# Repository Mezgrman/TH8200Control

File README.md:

# What's this?
A custom controller board for the Siemens TH8200 hand dryer.

# BOM
You can find the interactive BOM [here](https://mezgrman.github.io/TH8200Control/Hardware/bom/ibom.html).

# Pictures

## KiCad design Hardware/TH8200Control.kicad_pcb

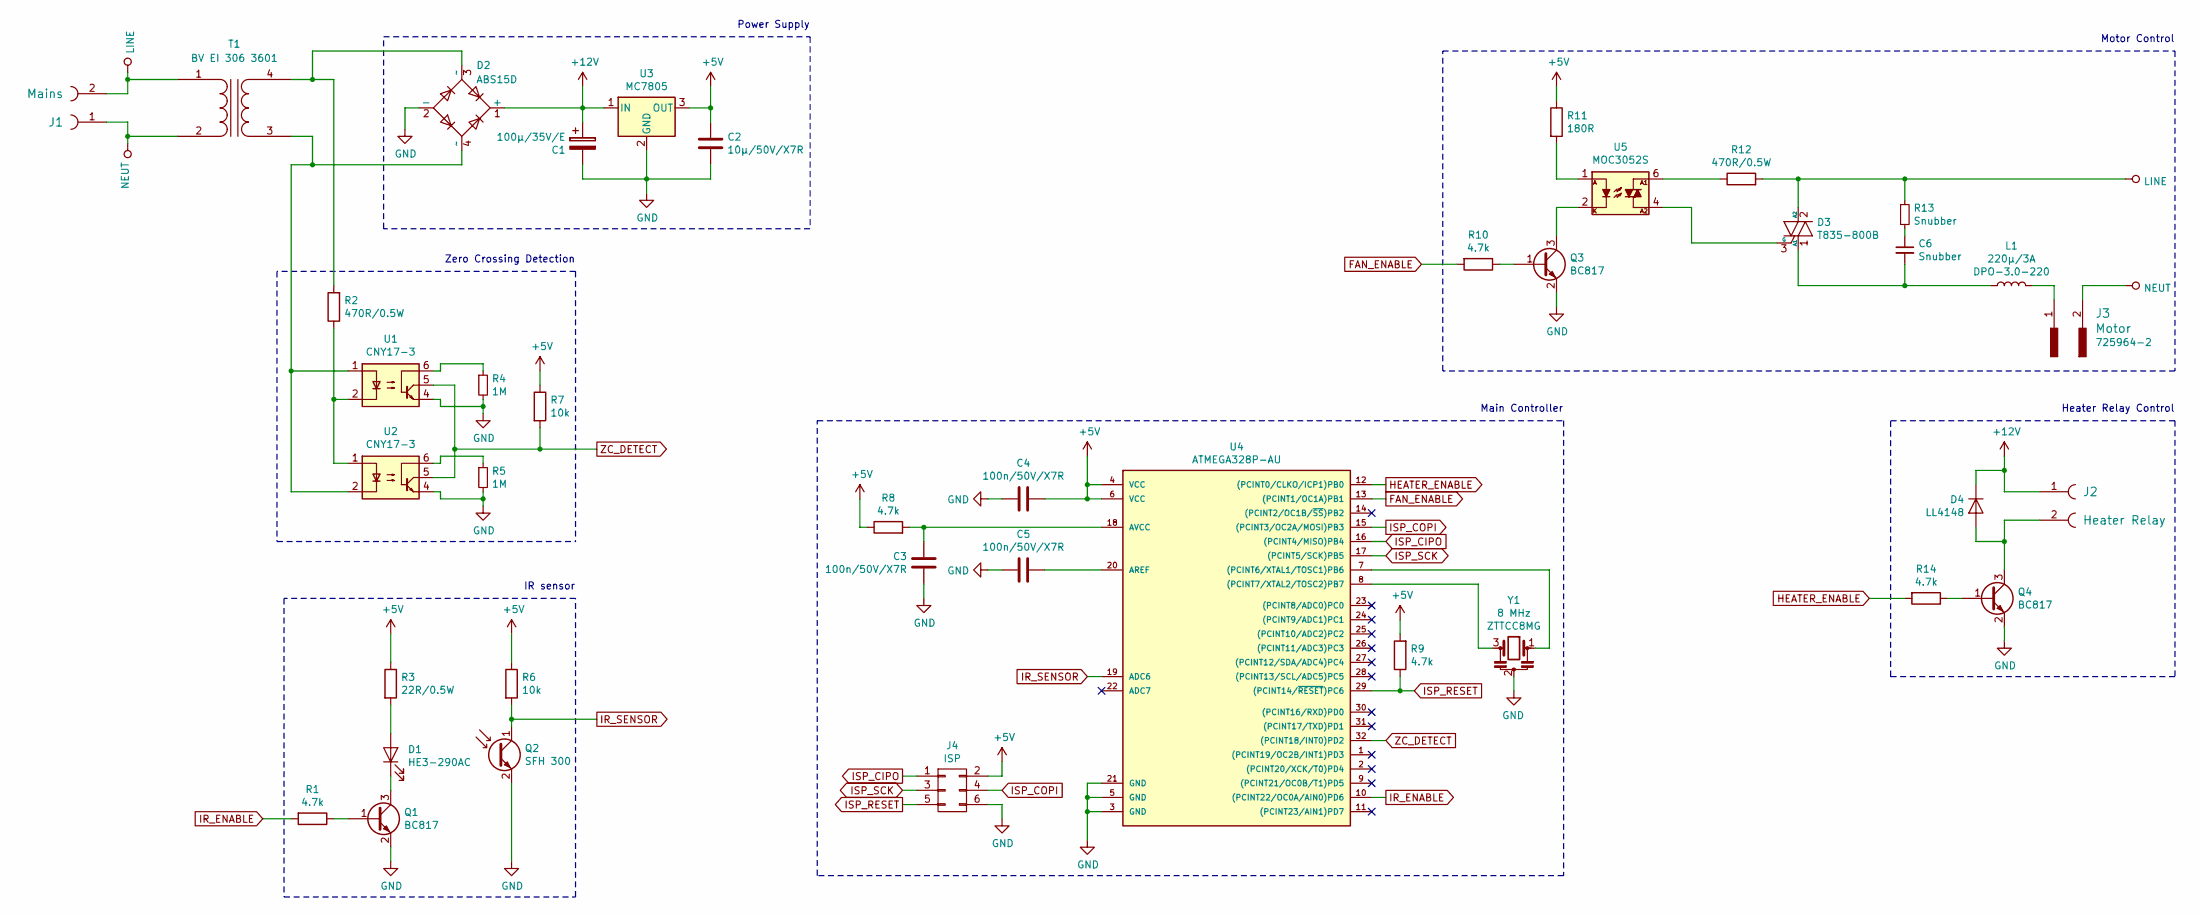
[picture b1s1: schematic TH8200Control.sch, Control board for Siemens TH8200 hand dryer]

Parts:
C1: 100µ/35V/E; CP_Elec_6.3x7.7
C2: 10µ/50V/X7R; C_1206
C3, C4, C5: 100n/50V/X7R; C_0603
C6: Snubber; C_0805
D1: HE3-290AC; LED_D5.0mm_Horicontal_O5.08mm
D2: ABS15D; Rectifier_SMD_4pin_ABS
D3: T835-800B; TO-252-2Lead
D4: LL4148; D_MiniMELF_Standard
J1: Mains; 2_Cables_D1.5mm_P10mm
J2: Heater Relay; 2_Cables_D1.5mm_P10mm
J3: Motor; FASTON_2pin_6.3x0.8mm_P10mm
J4: ISP; Pin_Header_Straight_SMT_02x03
L1: 220µ/3A; Choke_Toroid_13x29mm_Vertical
Q1, Q3, Q4: BC817; SOT-23
Q2: SFH 300; LED_D5.0mm_Horicontal_O5.08mm
R1, R8, R9, R10, R14: 4.7k; R_0603
R2, R12: 470R/0.5W; R_1206
R3: 22R/0.5W; R_1206
R4, R5: 1M; R_0603
R6, R7: 10k; R_0603
R11: 180R; R_0603
R13: Snubber; R_0603
T1: BV EI 306 3601; Transformer_Hahn_BVEI3063601
U1, U2: CNY17-3; Optocoupler_SMD_6pin
U3: MC7805; TO-263-3Lead
U4: ATMEGA328P-AU; TQFP-32_7x7mm_Pitch0.8mm
U5: MOC3052S; Optocoupler_SMD_6pin
Y1: 8 MHz; Resonator_ZTTCC_X.XX_MG

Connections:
+5V: C2.1, C4.1, J4.2, R3.1, R6.1, R7.1, R8.1, R9.2, R11.1, U3.3 (OUT), U4.4 (VCC), U4.6 (VCC)
+12V: C1.1, D2.1 (+), D4.1 (K), J2.1, U3.1 (IN)
FAN_ENABLE: R10.2, U4.13 ((PCINT1/OC1A)PB1)
GND: C1.2, C2.2, C3.1, C4.2, C5.2, D2.2 (-), J4.6, Q1.2 (E), Q2.2 (E), Q3.2 (E), Q4.2 (E), R4.2, R5.2, U1.4, U2.4, U3.2 (GND), U4.3 (GND), U4.5 (GND), U4.21 (GND), Y1.2
HEATER_ENABLE: R14.2, U4.12 ((PCINT0/CLKO/ICP1)PB0)
IR_ENABLE: R1.2, U4.10 ((PCINT22/OC0A/AIN0)PD6)
IR_SENSOR: Q2.1 (C), R6.2, U4.19 (ADC6)
ISP_CIPO: J4.1, U4.16 ((PCINT4/MISO)PB4)
ISP_COPI: J4.4, U4.15 ((PCINT3/OC2A/MOSI)PB3)
ISP_RESET: J4.5, R9.1, U4.29 ((PCINT14/~RESET~)PC6)
ISP_SCK: J4.3, U4.17 ((PCINT5/SCK)PB5)
LINE: D3.2 (A2), J1.2, R12.2, R13.1, T1.1 (AA)
NEUT: J1.1, J3.2, T1.2 (AB)
unnamed: C3.2, R8.2, U4.18 (AVCC)
unnamed: C5.1, U4.20 (AREF)
unnamed: C6.1, R13.2
unnamed: C6.2, D3.1 (A1), L1.1
unnamed: D1.1 (K), Q1.3 (C)
unnamed: D1.2 (A), R3.2
unnamed: D2.3 (~~), R2.2, T1.4 (SB)
unnamed: D2.4 (~~), T1.3 (SA), U1.1, U2.2
unnamed: D3.3 (G), U5.4
unnamed: D4.2 (A), J2.2, Q4.3 (C)
unnamed: J3.1, L1.2
unnamed: Q1.1 (B), R1.1
unnamed: Q3.1 (B), R10.1
unnamed: Q3.3 (C), U5.2
unnamed: Q4.1 (B), R14.1
unnamed: R2.1, U1.2, U2.1
unnamed: R4.1, U1.6
unnamed: R5.1, U2.6
unnamed: R11.2, U5.1
unnamed: R12.1, U5.6
unnamed: U4.7 ((PCINT6/XTAL1/TOSC1)PB6), Y1.1
unnamed: U4.8 ((PCINT7/XTAL2/TOSC2)PB7), Y1.3
ZC_DETECT: R7.2, U1.5, U2.5, U4.32 ((PCINT18/INT0)PD2)

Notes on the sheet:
Zero Crossing Detection
Power Supply
Motor Control
Heater Relay Control
IR sensor
Main Controller

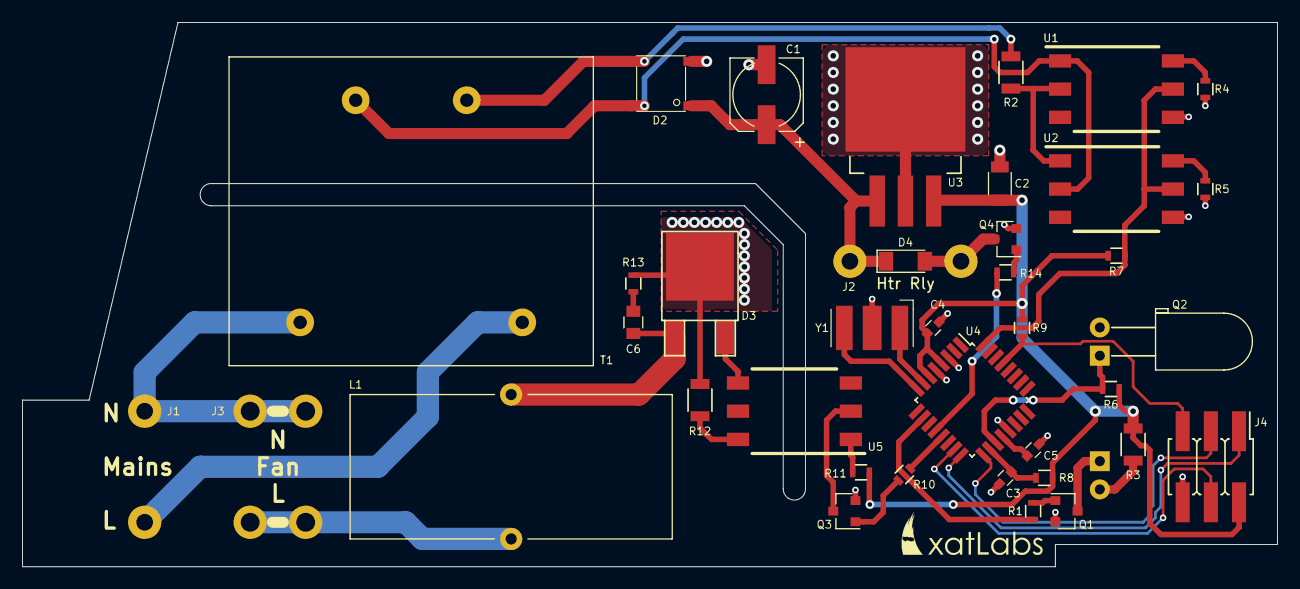
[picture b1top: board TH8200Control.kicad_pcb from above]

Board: 2 copper layers, 113.0 x 49.0 mm, 40 parts (1 on the bottom side), 36 nets.

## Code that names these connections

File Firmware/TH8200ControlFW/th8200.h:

/*
 * th8200.h
 *
 * Created: 29.07.2020 18:51:35
 *  Author: Julian Metzler
 */ 


#ifndef TH8200_H_
#define TH8200_H_

#include <stdint.h>

#define PORT_HTR_EN PORTB
#define PORT_FAN_EN PORTB
#define PORT_ZC_DET PORTD
#define PORT_IR_EN PORTD

#define DDR_HTR_EN DDRB
#define DDR_FAN_EN DDRB
#define DDR_ZC_DET DDRD
#define DDR_IR_EN DDRD

#define PIN_HTR_EN PB0
#define PIN_FAN_EN PB1
#define PIN_ZC_DET PD2
#define PIN_IR_EN PD6

#define INT_ZC_DET INT0
#define ISC_ZC_DET1 ISC01
#define ZC_DET_vect INT0_vect

void th8200_init(void);
void th8200_loop(void);
void th8200_setFanLevel(uint16_t level);
uint16_t th8200_getIRLevel(void);
uint8_t th8200_getIRState(void);
void th8200_setIR(uint8_t state);
void th8200_setHeater(uint8_t state);
void th8200_setFan(uint8_t state);

#endif /* TH8200_H_ */

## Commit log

2020-07-20 Add interactive BOM
2020-07-20 Add readme
2020-07-20 Add OSHW logo and GitHub link to PCB
2020-07-20 Update readme with images
2020-07-20 Update BOM
2020-07-20 Dark mode in BOM
2020-07-22 Add ISP header
2020-07-29 Fix polarity of C1
2020-07-30 Add firmware
2020-08-11 FW: Add always-on mode
